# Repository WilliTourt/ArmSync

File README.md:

# ArmSync

ArmSync is a six-degree-of-freedom robotic arm project using a dual-IMU master-slave wireless teleoperation scheme. It was originally developed for the Renesas Electronics Competition.

This repository contains mechanical design files, PCBs, embedded firmware, kinematics tools, and UI resources. You are welcome to reference the designs and code, but please note that the project is still being organized and iterated.

> **The design report PDF file is here：[Design Report](./Helpful%20Docs/设计报告%20Design%20Report.pdf)**

**⚠ WARNING: The software resources in this repository are provided for reference only.**

[中文文档](README-zh-CN.md)

---

## Overview

ArmSync is a six-degree-of-freedom robotic arm primarily made from PLA 3D-printed parts. It contains six mechanical joints, J1–J6, and supports configurable end effectors.

Main features:

- **Six degrees of freedom**: J1 base rotation, J2 shoulder pitch, J3 shoulder yaw, J4 elbow, J5 wrist pitch, and J6 wrist rotation
- **Dual-IMU master-slave control**: Uses user-side IMU modules to obtain upper-arm and forearm attitude for wireless/serial master-slave control
- **Stepper-motor actuators**: J1–J6 use stepper motors, gearboxes, and motor controllers
- **Configurable end effector**: A gripper is provided in the 3D resources, and other custom end effectors can also be installed

## Specifications

| Parameter | Value |
|------|------|
| Arm degrees of freedom | 6 (J1–J6) |
| Reach (including gripper) | Approximately 610mm |
| Target end-effector payload | 350g |
| Control interface | CAN bus / servo signal |
| Power supply | 24VDC (stepper motors) / 5VDC (servo) |
| Structural material | PLA 3D-printed parts |

## Repository Structure

```
ArmSync/
├── Hardware/                         # Mechanical, electrical, and assembly resources
│   ├── 3D Files/                     # Robot arm, gripper, and controller 3D models
│   │   ├── 3MF for printing/         # 3MF files ready for slicing
│   │   ├── SolidWorks 2026/          # SolidWorks source files
│   │   ├── STEP and STL/             # STEP/STL universal formats
│   │   └── URDF/                     # ROS/Gazebo model
│   ├── PCBs/                         # PCB projects and images
│   ├── example_imgs/                 # J1–J6 and EE assembly illustrations
│   ├── Parts BOM-zh-CN.md            # Chinese bill of materials
│   ├── Assembly Guide-zh-CN.md       # Chinese assembly guide
│   └── readme-zh-CN.md               # Hardware documentation
├── Software/                         # Firmware, kinematics tools, and UI resources
│   ├── Arm-Side/                     # RA8P1 robot-arm controller project
│   │   ├── Solution/                 # e² studio Solution, CPU0, and CPU1 projects
│   │   ├── arm_ik_test.py            # IK visualization tool for Jetson input
│   │   ├── arm_angle_view.py         # Joint-angle and spatial-vector visualization tool
│   │   └── Scripts README-zh-CN.md   # Python tools usage guide
│   ├── User-Side/                    # RA4M1 user-side controller and IMU projects
│   ├── Deprecated Project Folders/   # Deprecated projects
│   ├── UI/                           # HMI, UI layout, and font resources
│   └── readme-zh-CN.md               # Software documentation
├── Helpful Docs/                     # Reference material for MCU, NPU, HMI, and dual-core development
├── LICENSE
├── README-zh-CN.md
└── README.md
```

## Quick Start

### Hardware

- [Hardware documentation](Hardware/readme-zh-CN.md): Hardware specifications, directory structure, and resource descriptions
- [Bill of materials](Hardware/Parts%20BOM-zh-CN.md): Motors, gearboxes, fasteners, and development tools
- [Assembly guide](Hardware/Assembly%20Guide-zh-CN.md): Arm assembly, gripper, timing belts, and wiring
- [3D files](Hardware/3D%20Files/): SolidWorks, STEP/STL, 3MF, and URDF files
- [PCB resources](Hardware/PCBs/): Controller, IMU, and RA8P1 extension-board resources

For printing the mechanical parts, use:

`Hardware/3D Files/3MF for printing/Renesas ArmSync.3mf`

You can also use the universal models in `STEP and STL/` or modify the source files in `SolidWorks 2026/`.

### Software

Read the [software documentation](Software/readme-zh-CN.md) to understand the current project structure and toolchains:

- The RA8P1 controller uses e² studio and consists of the Solution, CPU0, and CPU1 projects
- The RA4M1 controller and IMU use CMake, Ninja, and VS Code
- The robot-arm Python tools are described in [Scripts README-zh-CN.md](Software/Arm-Side/Scripts%20README-zh-CN.md)
- The robot-arm coordinate system and kinematics parameters are described in [Armsync_IK_Model.md](Software/Arm-Side/Armsync_IK_Model.md)

Make sure that the FSP, Arm GCC toolchain, serial-port configuration, and actual hardware version are compatible.

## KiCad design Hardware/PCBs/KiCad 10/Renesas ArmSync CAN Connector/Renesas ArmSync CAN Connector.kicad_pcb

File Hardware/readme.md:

# Hardware Documentation - ArmSync 6-DOF Robotic Arm

This directory contains all hardware-related files for the ArmSync six-degree-of-freedom robotic arm project.

[中文文档](/Hardware/readme-zh-CN.md)

## Project Overview

ArmSync is a six-degree-of-freedom robotic arm with dual-IMU master-slave wireless teleoperation. The project focuses on cost-effectiveness and ease of replication.

### Main Specifications

| Parameter | Value |
|-----------|-------|
| Degrees of freedom | 6 (J1-J6) |
| Reach (including gripper) | ~610mm |
| End-effector payload | 350g (target) |
| Control interface | CAN bus / servo signal |
| Power supply | 24VDC (stepper motors) / 5VDC (servo) |

### Joint Configuration

| Joint | Name | Motor | Gear Ratio | Function |
|-------|------|-------|------------|----------|
| J1 | Base rotation | 57×76mm stepper motor | 20:1 | Base rotation |
| J2 | Shoulder pitch | 42×60mm stepper motor | 30:1 | Shoulder up/down |
| J3 | Shoulder yaw | 42×40mm stepper motor | 10:1 | Shoulder left/right |
| J4 | Elbow | 42×48mm stepper motor | 10:1 | Elbow bending |
| J5 | Wrist pitch | 42×40mm stepper motor | 10:1 or 5:1 | Wrist up/down |
| J6 | Wrist rotation | 42×34mm stepper motor | - | Wrist rotation |
| EE | Gripper | MG90S servo or any other end effector | - | End effector |

## Directory Structure

```
Hardware/
├── 3D Files/              # All 3D model files
│   ├── 3MF for printing/  # Ready-to-print 3MF files
│   ├── SolidWorks 2026/   # Original SolidWorks source files
│   ├── STEP and STL/      # Exported universal-format files
│   └── URDF/              # URDF files
├── Parts BOM.md           # Bill of materials and prices
├── Assembly Guide.md      # Step-by-step assembly instructions
└── readme.md              # This file
```

## Quick Start

### 1. Review the Design

See the [3D Files](./3D%20Files/) directory for the complete mechanical design files:
- **SolidWorks 2026/**: Original editable source files
- **STEP and STL/**: Universal formats for viewing and printing
- **3MF for printing/**: Pre-configured Bambu Studio project files
- **URDF/**: Robotic-arm model for ROS and other simulation tools

See the [PCB schematics and layouts](./PCBs/) directory for the required board files:
- **EasyEDA_LCEDA/**: Controller PCB, wearable IMU sensor PCB, and extension-board files for the Renesas CPKHMI-RA8P1 board
- **Imgs/**: Screenshots of schematics and PCBs
- **KiCad 10/**: Boards for the stepper-motor CAN bus / servo-signal connectors. These boards are designed to plug into each ZDT stepper-motor controller and relay the wiring.

### 2. Purchase Parts

See [Parts BOM.md](./Parts%20BOM.md) for the complete parts list, including:
- Motor specifications and prices
- Gearbox selection guide
- Fastener quantities
- Estimated total cost (approximately RMB 1,500)

### 3. 3D Printing

**Recommended print settings:**
- Material: PLA Basic or better
- Layer height: 0.18mm
- Infill: 35–60% (structural parts), 20% (cosmetic parts)
- Supports: Add as needed

**Note: Some M2.5 holes used to connect couplings may be undersized. Check the bore of the coupling you purchase and consider enlarging the holes to M3 if necessary.**

### 4. Assembly

Follow the [Assembly Guide.md](./Assembly%20Guide.md) for step-by-step assembly:
- Assembly order: from top to bottom: J1 → J2 → J3 → J4 → J5 → J6 → EE
- Fastener specifications
- Wiring

## Support

For questions about hardware assembly:
1. Check the [Assembly Guide](./Assembly%20Guide.md)
2. Submit an issue on GitHub
3. Contact me by email or through other social media.

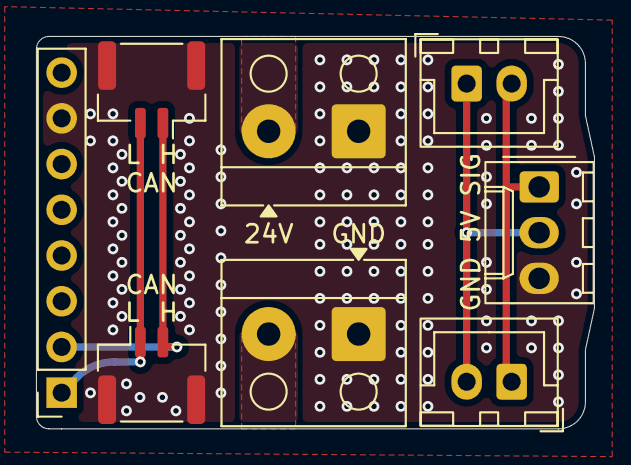
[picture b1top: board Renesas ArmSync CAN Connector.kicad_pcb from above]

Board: 2 copper layers, 31.0 x 21.8 mm, 8 parts (0 on the bottom side), 6 nets.

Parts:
24V: PWR24; Altech_AK100_1x02_P5.00mm
CAN: CAN; JST_GH_SM02B-GHS-TB_1x02-1MP_P1.25mm_Horizontal
CAN#2: CAN; JST_GH_SM02B-GHS-TB_1x02-1MP_P1.25mm_Horizontal
GND 5V SIG: SERVO_OUT; Molex_KK-254_AE-6410-03A_1x03_P2.54mm_Vertical
J1: STEPPER_BUS; PinSocket_1x08_P2.54mm_Vertical
J3: PWR24; Altech_AK100_1x02_P5.00mm
J7, J8: SERVO_CABLE; JST_XH_B2B-XH-A_1x02_P2.50mm_Vertical

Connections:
+5V: GND 5V SIG.2, J7.1, J8.2
+24V: 24V.1, J1.8, J3.2
/CAN_H: CAN.1, CAN#2.2, J1.2
/CAN_L: CAN.2, CAN#2.1, J1.1
/SIGNAL: GND 5V SIG.1, J7.2, J8.1
GND: 24V.2, CAN.MP, CAN#2.MP, GND 5V SIG.3, J1.7, J3.1

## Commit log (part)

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2026-03-28 Added 3d model files
2026-03-28 software folder init
2026-03-28 updated readme.md, now work in progress
2026-04-01 Add hardware docs: assembly guides, BOMs, readmes
2026-04-01 added assemble_guide image examples, updated docs
2026-04-01 uploaded easyeda pcb projects
2026-04-02 uploaded user-end ctrller and imu keil project
2026-04-03 Uploaded arm-side project folder
2026-04-03 updated readme.md in /software
2026-04-03 Updated docs
2026-04-03 added language switch
